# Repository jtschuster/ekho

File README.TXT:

This repository contains the code required to run the ekho.

Folders:
    - pc_record: Teensy code and a real-time processing code to record the IV curves while connected to a computer. Includes a real-time plot of the IV curves.
    - mobile_record: Teensy code to record IV curves when disconnected from a computer, and code to convert the raw data from the SD card to useable formats.
    - emulate: Computer and teensy code necessary to emulate a recorded IV surface.
    
Requirements:
    - GSL (GNU Scientific Library). 
            This may need to be installed using Homebrew, even on Linux machines. 
            $ brew install gsl
    - OpenGL Utility Kit (GLUT)
            $ brew install freeglut
    - g++ and gcc
    - Arduino and Teensyduino
    - Make
    - GNUplot

File formats
.raw:
    This format is what the data from the recording is placed into. The data is in binary format and not readable by other programs. It can be converted into a text file using the tools in pc_record. It has the following format repeated for a number of timestamps:

    <timestamp, 1 double value> <voltages, 500 long double values> <currents, 500 long double values>

    The j'th voltage value corresponds to the j'th current value. Together, the 500 (voltage, current) points can be regressed to create an IV curve. 

    Note the .raw from pc_record and mobile_record are not the same format. mobile_record must go through a conversion to be the .raw decribed here. This is because of optimizations that are made to avoid floating point operatins on Teensy so to make the processing faster.

.ivs
    This format is used by the emulator. It is created by finding a regression of the .raw data points. It is also in unreadable binary format
    It has the following format repeated for a number of timestamps:

    <timestamp, 1 double value> <currents, 65 long double values>

    The voltages to go with the currents are predetermined. Where do these values come from ?
    10.8 volts is max voltage range can be produced by the emulator board and we have 65 points on x axis (voltage).
	 so 10.8/65 = 0.16615384615L. to get all 65 points value on x axis, 0.16615384615 is added to get next point on the axis.
    long double v=0;
    for (int j=1;j<65;j++)
    {
        v+=0.16615384615L; // 10.8(max voltage range)/65points
    }

.gnu
    gnuplot file of the recorded raw data or curve made from regression. See gnuplot online documentation for more info.

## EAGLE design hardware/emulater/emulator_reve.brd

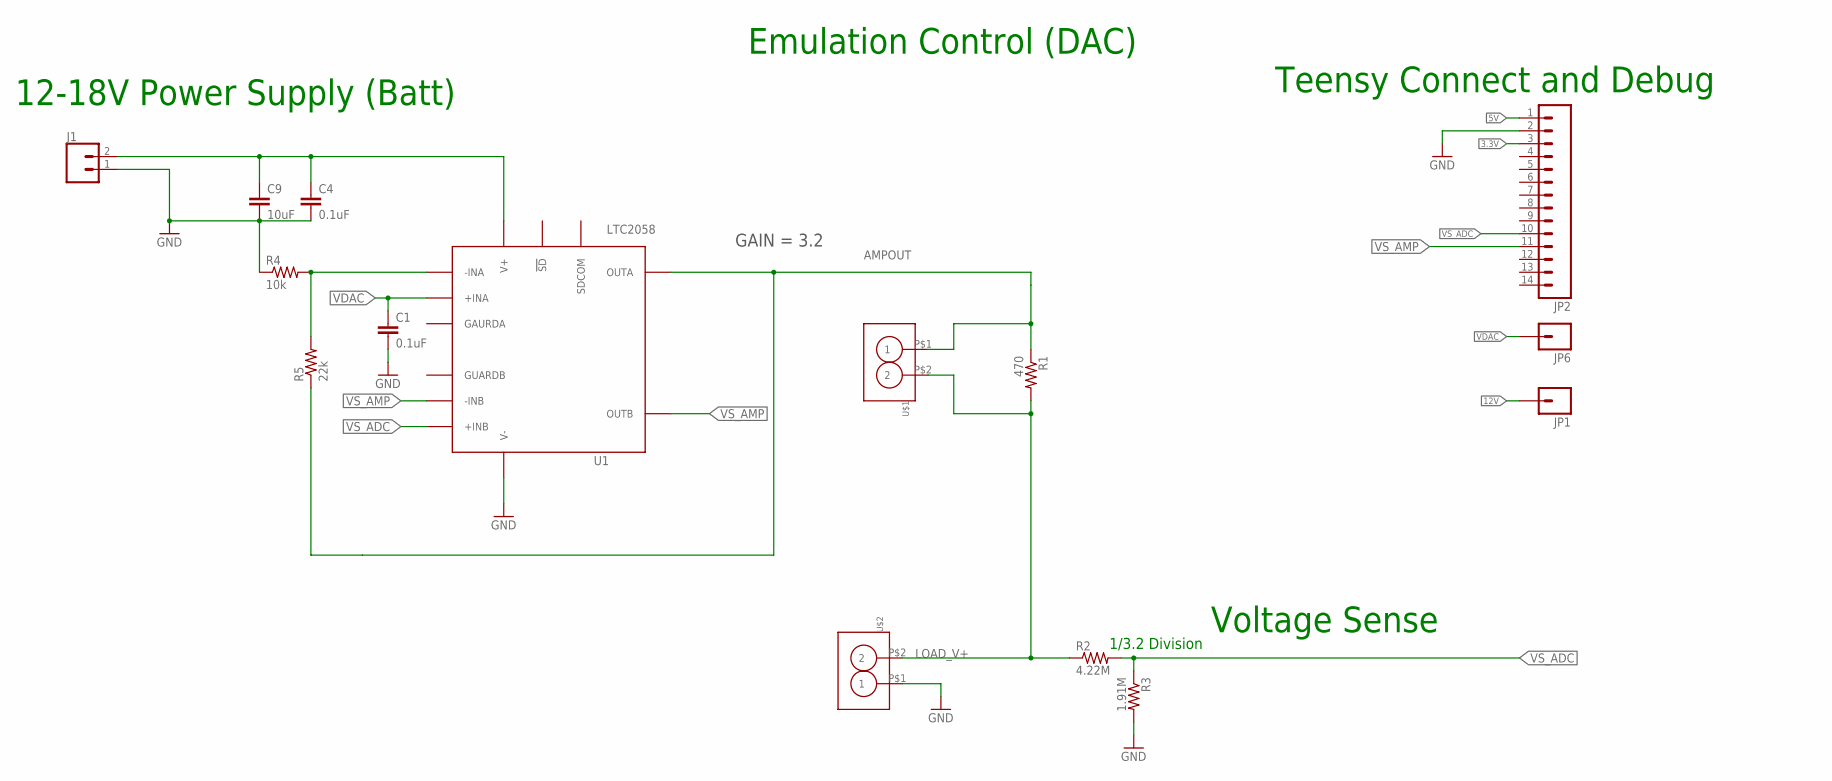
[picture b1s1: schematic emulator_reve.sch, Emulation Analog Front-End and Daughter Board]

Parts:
C1, C4: 0.1uF; 0603; DIGIKEY 490-3271-1-ND
C9: 10uF; 1210; DIGIKEY 490-1867-1-ND
J1: CONN_02; 1X02
JP1, JP6: M01PTH; 1X01
JP2: M14; 1X14
R1: 470; 0805
R2: 4.22M; 0603; DIGIKEY P2.0MJCT-ND
R3: 1.91M; 0603; DIGIKEY P2.0MJCT-ND
R4: 10k; 0603; DIGIKEY 311-40.2KLRCT-ND
R5: 22k; 0603; DIGIKEY 311-40.2KLRCT-ND
U1: LTC2058; MSOP12
U$1, U$2: SCREW_CONNECTOR-2PIN'; SCREW_CONNECTOR-2PIN-3.5MM

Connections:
3.3V: JP2.3
5V: JP2.1
12V: C4.1, C9.1, J1.2, JP1.1, U1.11 (V+)
AMPOUT: R1.1, R5.1, U1.3 (OUTA), U$1.P$1 (1)
GND: C1.2, C4.2, C9.2, J1.1, JP2.2, R3.2, R4.1, U1.2 (V-), U1.EXP (V-), U$2.P$1 (1)
INA-: R4.2, R5.2, U1.5 (-INA)
LOAD_V+: R1.2, R2.1, U$1.P$2 (2), U$2.P$2 (2)
VDAC: C1.1, JP6.1, U1.6 (+INA)
VS_ADC: JP2.10, R2.2, R3.1, U1.7 (+INB)
VS_AMP: JP2.11, U1.8 (-INB), U1.10 (OUTB)

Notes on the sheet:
Voltage Sense
1/3.2 Division
Emulation Control (DAC)
12-18V Power Supply (Batt)
GAIN = 3.2
Teensy Connect and Debug

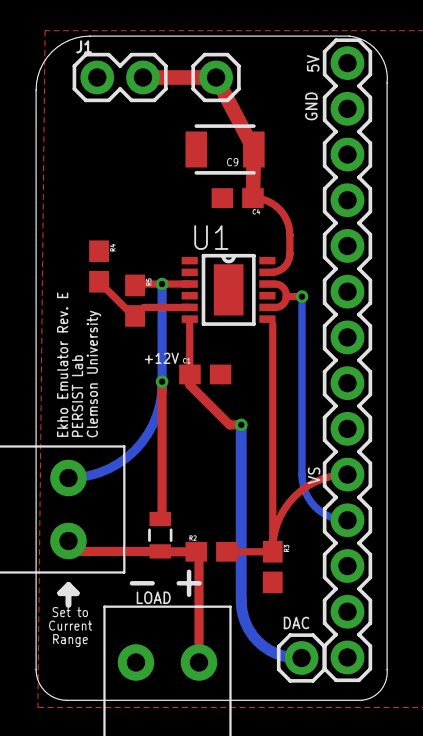
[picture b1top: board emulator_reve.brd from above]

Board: 2 copper layers, 19.5 x 36.9 mm, 15 parts (0 on the bottom side), 8 nets.

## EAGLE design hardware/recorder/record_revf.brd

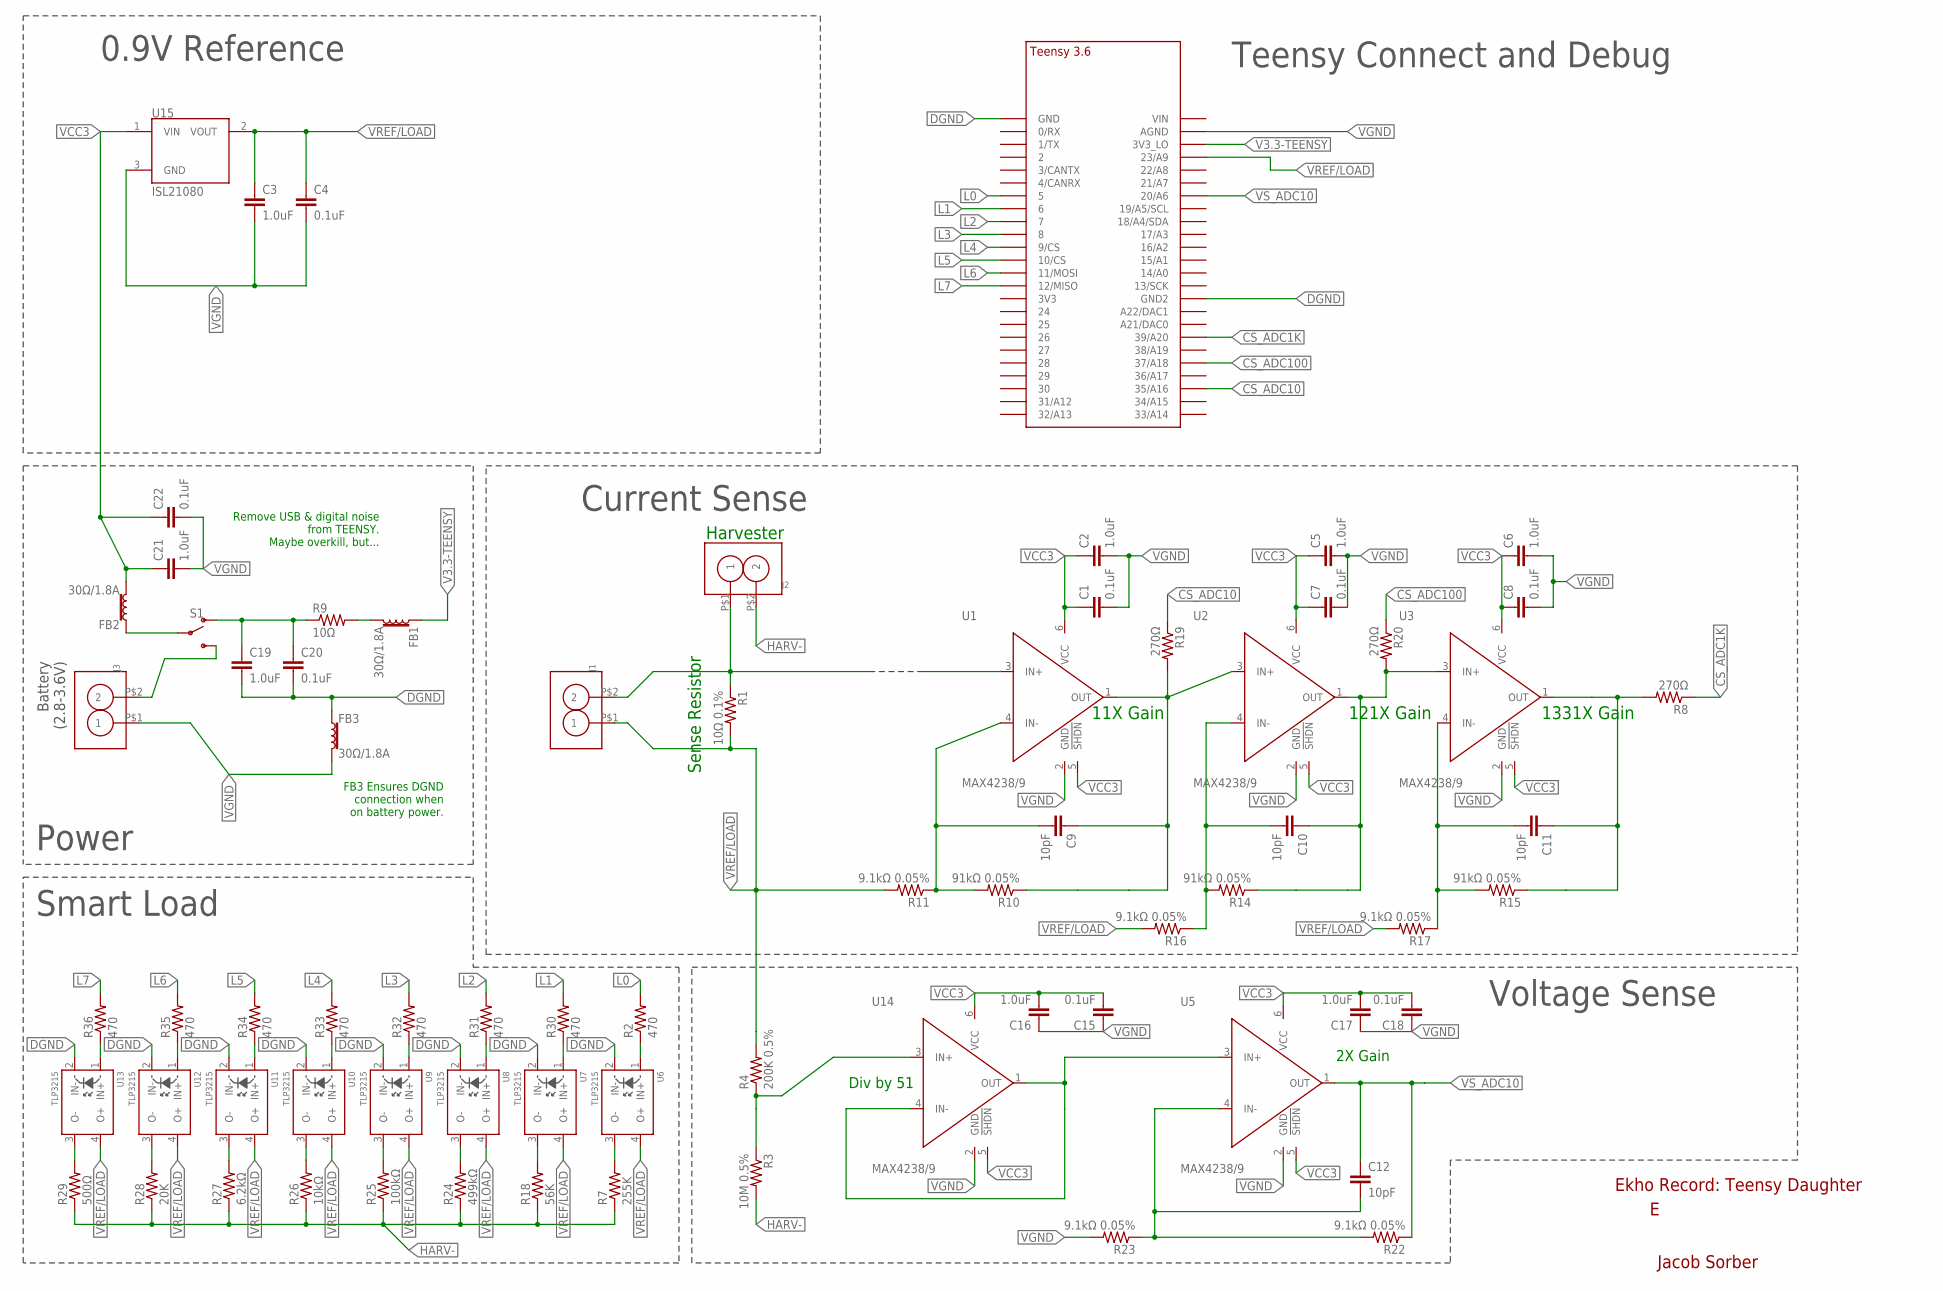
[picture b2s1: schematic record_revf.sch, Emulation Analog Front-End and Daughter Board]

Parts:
C1, C4, C7, C8, C15, C18, C20, C22: 0.1uF; 0603; DIGIKEY 490-3271-1-ND
C2, C3, C5, C6, C16, C17, C19, C21: 1.0uF; 0603; DIGIKEY 490-3890-1-ND
C9, C10, C11, C12: 10pF; 0603; DIGIKEY 490-3271-1-ND
FB1, FB2, FB3: 30Ω/1.8A; 0603
J1, J2, J3: SCREW_CONNECTOR-2PIN'; SCREW_CONNECTOR-2PIN-3.5MM
R1: 10Ω 0.1%; 0805
R2, R30, R31, R32, R33, R34, R35, R36: 470; 0603; DIGIKEY P2.0MJCT-ND
R3: 10M 0.5%; 0603; DIGIKEY P2.0MJCT-ND
R4: 200K 0.5%; 0603; DIGIKEY P2.0MJCT-ND
R7: 255K; 0603; DIGIKEY P2.0MJCT-ND
R8, R19, R20: 270Ω; 0603; DIGIKEY P2.0MJCT-ND
R9: 10Ω; 0805
R10, R14, R15: 91kΩ 0.05%; 0603; DIGIKEY P2.0MJCT-ND
R11, R16, R17, R22, R23: 9.1kΩ 0.05%; 0603; DIGIKEY P2.0MJCT-ND
R18: 56K; 0603; DIGIKEY P2.0MJCT-ND
R24: 499kΩ; 0603; DIGIKEY P2.0MJCT-ND
R25: 100kΩ; 0603; DIGIKEY P2.0MJCT-ND
R26: 10kΩ; 0603; DIGIKEY P2.0MJCT-ND
R27: 6.2kΩ; 0603; DIGIKEY P2.0MJCT-ND
R28: 20K; 0603; DIGIKEY P2.0MJCT-ND
R29: 500Ω; 0603; DIGIKEY P2.0MJCT-ND
S1: SWITCH-SPDT-PTH-11.6X4.0MM-KIT; SWITCH_SPDT_PTH_11.6X4.0MM_KIT
U1, U2, U3, U5, U14: MAX4238/9; SOT23-6
U6, U7, U8, U9, U10, U11, U12, U13: TLP3215
U15: ISL21080; SOT-23
U$6: TEENSY_3.5/3.6_SIDE_ONLY

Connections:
CS_ADC1K: R8.1, U$6.39/A20
CS_ADC10: R19.1, U$6.35/A16
CS_ADC100: R20.1, U$6.37/A18
DGND: C19.2, C20.2, FB3.1, U6.2 (IN-), U7.2 (IN-), U8.2 (IN-), U9.2 (IN-), U10.2 (IN-), U11.2 (IN-), U12.2 (IN-), U13.2 (IN-), U$6.GND, U$6.GND2
HARV+: J1.P$2 (2), J2.P$1 (1), R1.1, U1.3 (IN+)
HARV-: J2.P$2 (2), R3.2, R7.1, R18.1, R24.1, R25.1, R26.1, R27.1, R28.1, R29.1
L0: R2.2, U$6.5
L1: R30.2, U$6.6
L2: R31.2, U$6.7
L3: R32.2, U$6.8
L4: R33.2, U$6.9/CS
L5: R34.2, U$6.10/CS
L6: R35.2, U$6.11/MOSI
L7: R36.2, U$6.12/MISO
unnamed: C9.2, R10.2, R11.1, U1.4 (IN-)
unnamed: R3.1, R4.1, U14.3 (IN+)
unnamed: U5.3 (IN+), U14.1 (OUT), U14.4 (IN-)
unnamed: C19.1, C20.1, R9.1, S1.1 (O)
unnamed: FB1.2, R9.2
unnamed: R29.2, U13.3 (O-)
unnamed: J3.P$2 (2), S1.3 (S)
unnamed: C12.2, R22.2, R23.1, U5.4 (IN-)
unnamed: FB2.1, S1.2
unnamed: R28.2, U12.3 (O-)
unnamed: R27.2, U11.3 (O-)
unnamed: C10.2, R14.2, R16.1, U2.4 (IN-)
unnamed: C11.2, R15.2, R17.1, U3.4 (IN-)
unnamed: R26.2, U10.3 (O-)
unnamed: R25.2, U9.3 (O-)
unnamed: R24.2, U8.3 (O-)
unnamed: R18.2, U7.3 (O-)
unnamed: R7.2, U6.3 (O-)
unnamed: R2.1, U6.1 (IN+)
unnamed: R30.1, U7.1 (IN+)
unnamed: R31.1, U8.1 (IN+)
unnamed: R32.1, U9.1 (IN+)
unnamed: R33.1, U10.1 (IN+)
unnamed: R34.1, U11.1 (IN+)
unnamed: R35.1, U12.1 (IN+)
unnamed: R36.1, U13.1 (IN+)
OUT1K: C11.1, R8.2, R15.1, U3.1 (OUT)
OUT10: C9.1, R10.1, R19.2, U1.1 (OUT), U2.3 (IN+)
OUT100: C10.1, R14.1, R20.2, U2.1 (OUT), U3.3 (IN+)
V3.3-TEENSY: FB1.1, U$6.3V3_LO
VCC3: C1.1, C2.1, C5.1, C6.1, C7.1, C8.1, C15.2, C16.2, C17.2, C18.2, C21.1, C22.1, FB2.2, U1.5 (!SHDN), U1.6 (VCC), U2.5 (!SHDN), U2.6 (VCC), U3.5 (!SHDN), U3.6 (VCC), U5.5 (!SHDN), U5.6 (VCC), U14.5 (!SHDN), U14.6 (VCC), U15.1 (VIN)
VGND: C1.2, C2.2, C3.2, C4.2, C5.2, C6.2, C7.2, C8.2, C15.1, C16.1, C17.1, C18.1, C21.2, C22.2, FB3.2, J3.P$1 (1), R23.2, U1.2 (GND), U2.2 (GND), U3.2 (GND), U5.2 (GND), U14.2 (GND), U15.3 (GND), U$6.AGND
VREF/LOAD: C3.1, C4.1, J1.P$1 (1), R1.2, R4.2, R11.2, R16.2, R17.2, U6.4 (O+), U7.4 (O+), U8.4 (O+), U9.4 (O+), U10.4 (O+), U11.4 (O+), U12.4 (O+), U13.4 (O+), U15.2 (VOUT), U$6.23/A9
VS_ADC10: C12.1, R22.1, U5.1 (OUT), U$6.20/A6

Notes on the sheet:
Sense Resistor
Voltage Sense
Current Sense
2X Gain
Teensy Connect and Debug
Harvester
Smart Load
Jacob Sorber
Ekho Record: Teensy Daughter
0.9V Reference
11X Gain
121X Gain
1331X Gain
Div by 51
Battery (2.8-3.6V)
FB3 Ensures DGND connection when on battery power.
Remove USB & digital noise from TEENSY. Maybe overkill, but...
Power

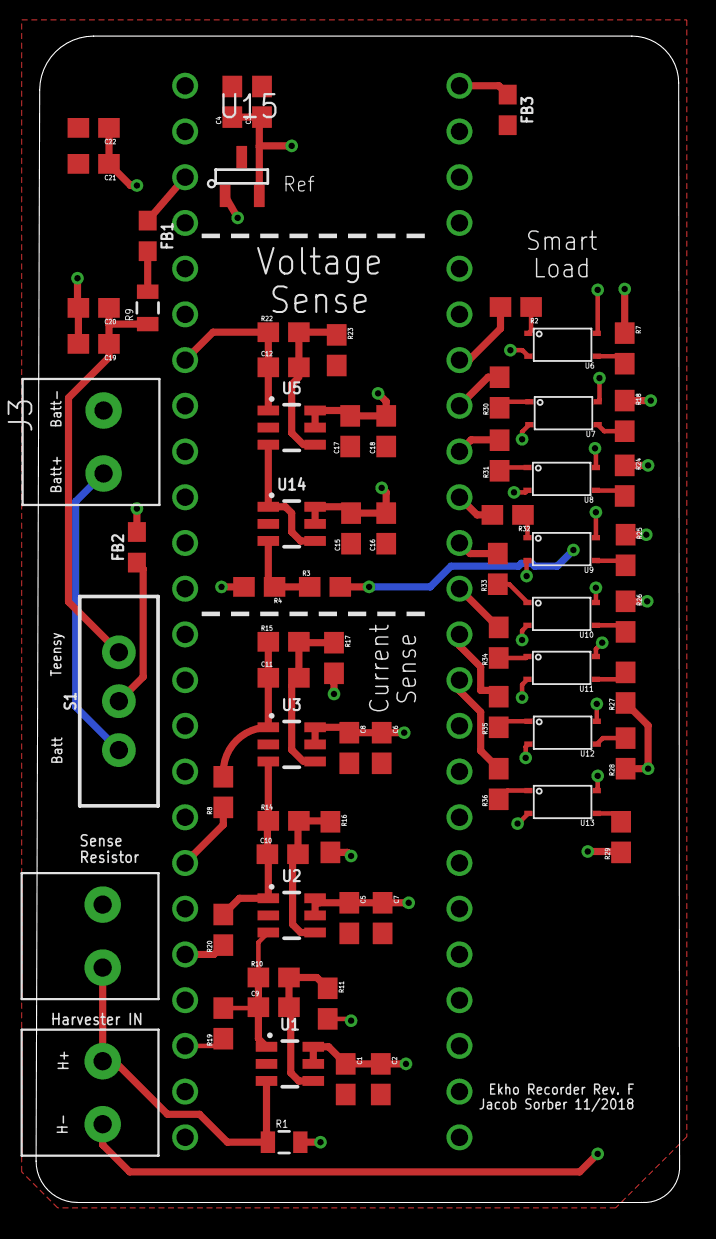
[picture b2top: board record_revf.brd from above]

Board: 4 copper layers, 35.8 x 64.8 mm, 73 parts (1 on the bottom side), 48 nets.

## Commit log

2019-11-20 Record works. Record outputs both .ivs and .raw
2019-11-22 forgot to add subdirectories
2019-12-19 Testing complete. Documentation in progress
2019-12-19 updates mse to report multiple errors
2019-12-19 added verification readme
2020-01-10 renamed files
2020-01-10 removed unnecessary files
2020-01-10 removed binaries
2020-01-14 removed redundancy from pc_record
2020-01-14 removed redundancy
2020-01-15 changed to 512 points from 500
2020-01-15 fixed plot_surface to account for 512 points
2020-01-15 few tweaks
2020-01-15 final from Jan 15 meeting
2020-01-16 added recursive makefiles
2020-01-16 forgot to git add makefiles last time
2020-01-16 started modifying ReadMes
2020-01-16 readded emulate.cpp
2020-01-16 changed files names
2020-01-16 removed unnecessary damap files
2020-01-16 moved dacmap
2020-01-16 changed dacmap location
2020-01-16 uncommented some code
2020-01-16 minor change
2020-01-16 local
2020-01-16 added more documentation
2020-01-16 formatted README
2020-01-16 minor changes
2020-01-16 more formatting
2020-01-16 added usage in README
2020-01-16 more changes in readme
2020-01-16 more changes in emulater readme
2020-01-17 more changes in mobile recorder readme
2020-01-17 changed file format
2020-01-17 more changes in mobile record readme
2020-01-17 started adding pc_recording documentation
2020-01-17 more comments on pc_recording
2020-01-17 gen_surface documentation
2020-01-17 tools documentation completed
2020-01-17 minor edits
2020-01-17 tools' documentation complete
2020-01-17 adding hardware files
2020-01-17 finished documentation
2020-01-18 edited makefiles for linux and minor changes
2020-01-18 made adjustments for linux
2020-01-18 changed a makefile
2020-01-18 edited makefiles again
2020-01-18 linux emulate and record working
2020-01-18 final check working
2020-01-19 readded old readme
2020-01-20 added where resistor goes on the emulate board
2020-01-20 testing readmes
2020-01-20 Update emulate readme
2020-01-20 fixed readme
2020-01-20 edited calculations in emulation readme

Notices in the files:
parts and their libraries:
SparkFun-Capacitors: Licensing: CC v3.0 Share-Alike You are welcome to use this library for commercial purposes.
SparkFun-Connectors: Licensing: Creative Commons ShareAlike 4.0 International - https://creativecommons.org/licenses/by-sa/4.0
